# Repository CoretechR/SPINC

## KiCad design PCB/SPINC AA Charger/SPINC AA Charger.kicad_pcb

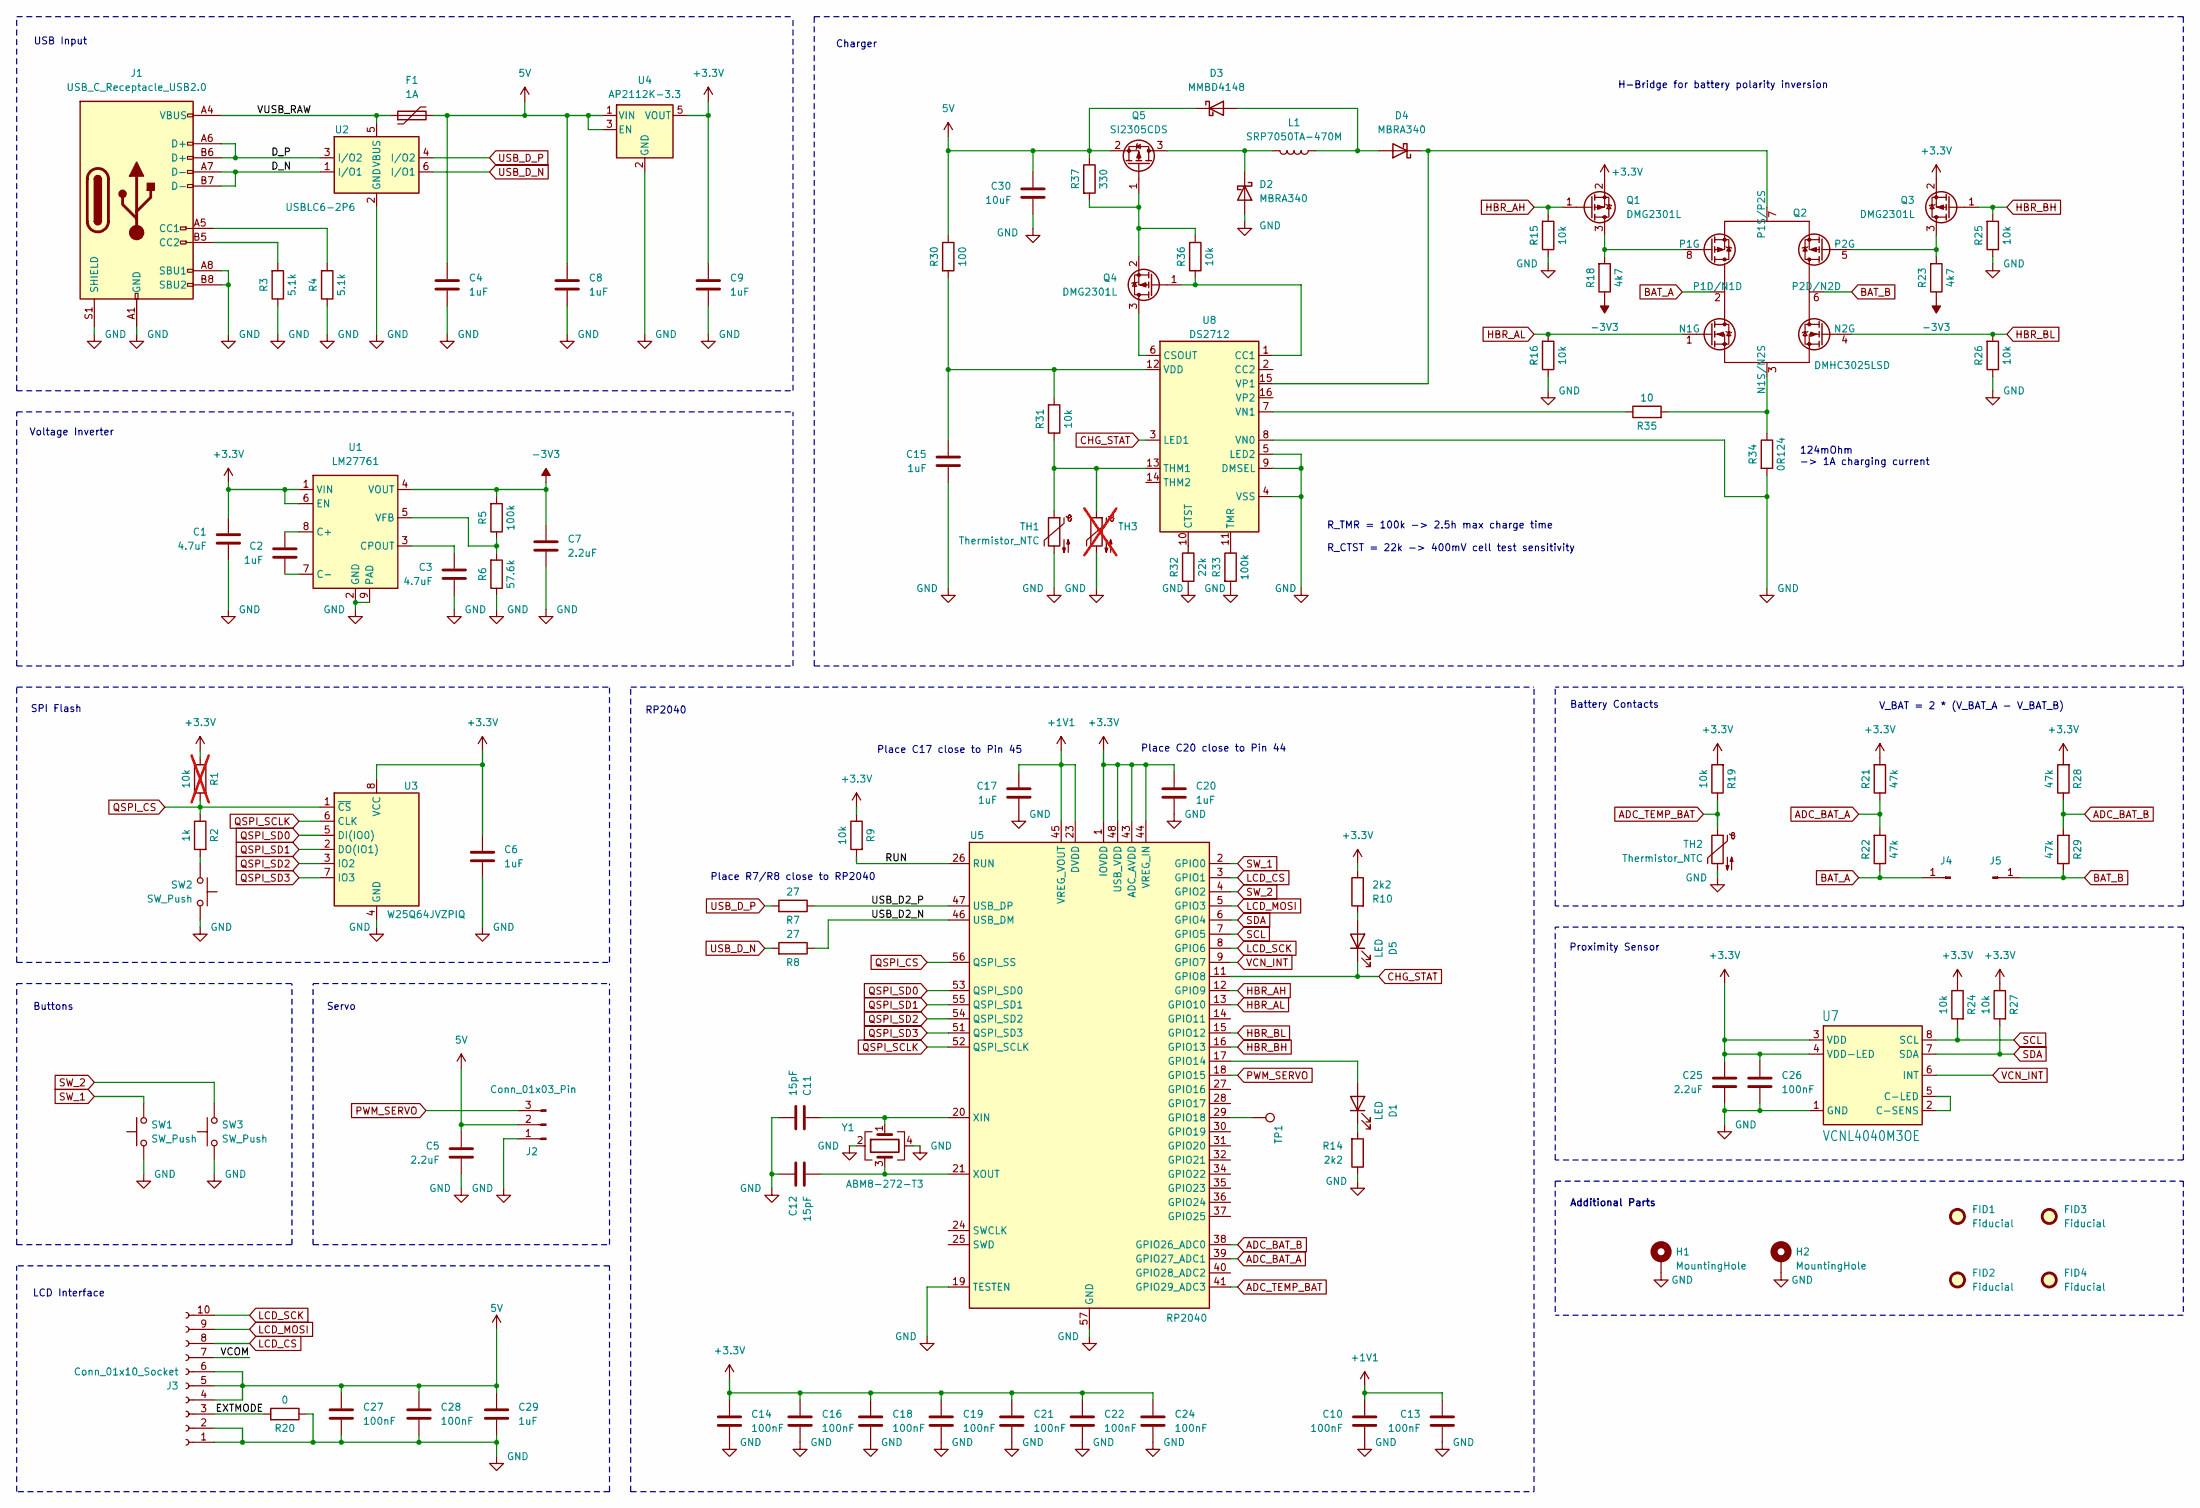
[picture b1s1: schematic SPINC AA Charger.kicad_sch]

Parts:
C1, C3: 4.7uF; C_0603_1608Metric; LCSC C1705
C2, C4, C6, C8, C9, C15, C17, C20, C29: 1uF; C_0603_1608Metric; LCSC C15849
C5, C7, C25: 2.2uF; C_0603_1608Metric; LCSC C913904
C10, C13, C14, C16, C18, C19, C21, C22, C24, C26, C27, C28: 100nF; C_0603_1608Metric; LCSC C1591
C11, C12: 15pF; C_0603_1608Metric; LCSC C107037
C30: 10uF; C_0603_1608Metric; LCSC C15850
D1, D5: LED; LED_0603_1608Metric; LCSC C965807
D2, D4: MBRA340; D_SMA; LCSC C26178
D3: MMBD4148; TSOT-23; LCSC C2928912
F1: 1A; Fuse_1206_3216Metric_Pad1.42x1.75mm_HandSolder; LCSC C151162
FID1, FID2, FID3, FID4: Fiducial; Fiducial_1mm_Mask2mm
H1, H2: MountingHole; MountingHole_3.2mm_M3_Pad_Via
J1: USB_C_Receptacle_USB2.0; USB_C_Receptacle_HRO_TYPE-C-31-M-12; LCSC C2982555
J2: Conn_01x03_Pin; PinHeader_1x03_P2.54mm_Vertical; LCSC C6332196
J3: Conn_01x10_Socket; 68711014022; LCSC C2919540
J4, J5: Conn_01x01_Pin; BatteryHolder_Keystone_590; LCSC C3029553
L1: SRP7050TA-470M; L_Bourns_SRP7050TA_7.3x6.6mm; LCSC C2047110
Q1, Q3, Q4: DMG2301L; SOT-23; LCSC C102619
Q2: DMHC3025LSD; SO-8_3.9x4.9mm_P1.27mm; LCSC C156387
Q5: SI2305CDS; SOT-23; LCSC C37577
R1: 10k; R_0603_1608Metric; not fitted
R2: 1k; R_0603_1608Metric; LCSC C22548
R3, R4: 5.1k; R_0603_1608Metric; LCSC C105580
R5, R33: 100k; R_0603_1608Metric; LCSC C14675
R6: 57.6k; R_0603_1608Metric; LCSC C245983
R7, R8: 27; R_0603_1608Metric; LCSC C137753
R9, R15, R16, R19, R24, R25, R26, R27, R31, R36: 10k; R_0603_1608Metric; LCSC C98220
R10, R14: 2k2; R_0603_1608Metric; LCSC C114662
R18, R23: 4k7; R_0603_1608Metric; LCSC C99782
R20: 0; R_0603_1608Metric; LCSC C116699
R21, R22, R28, R29: 47k; R_0603_1608Metric; LCSC C105579
R30: 100; R_0603_1608Metric; LCSC C125923
R32: 22k; R_0603_1608Metric; LCSC C114065
R34: 0R124; R_2512_6332Metric; LCSC C875831
R35: 10; R_0603_1608Metric; LCSC C109318
R37: 330; R_0603_1608Metric; LCSC C105881
SW1, SW3: SW_Push; Panasonic_EVQPUM_EVQPUD; LCSC C388642
SW2: SW_Push; SW_SPST_EVQP2; LCSC C2915174
TH1, TH2: Thermistor_NTC; R_0603_1608Metric; LCSC C13564
TH3: Thermistor_NTC; R_LDR_4.9x4.2mm_P2.54mm_Vertical; not fitted
TP1: TestPoint; TestPoint_Pad_D1.5mm
U1: LM27761; WSON-8-1EP_2x2mm_P0.5mm_EP0.9x1.6mm; LCSC C129351
U2: USBLC6-2P6; SOT-666; LCSC C2827693
U3: W25Q64JVZPIQ; WSON-8-1EP_6x5mm_P1.27mm_EP3.4x4.3mm; LCSC C2940197
U4: AP2112K-3.3; SOT-23-5; LCSC C51118
U5: RP2040; QFN-56-1EP_7x7mm_P0.4mm_EP3.2x3.2mm; LCSC C2040
U7: VCNL4040M3OE; VISHAY_VCNL4040_4X2X1.1; LCSC C142526
U8: DS2712; TSSOP-16_4.4x5mm_P0.65mm
Y1: ABM8-272-T3; Crystal_SMD_Abracon_ABM8G-4Pin_3.2x2.5mm; LCSC C20625731

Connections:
5V: C4.1, C5.1, C8.1, C27.1, C28.1, C29.1, C30.1, D3.3 (K), F1.2, J2.2, J3.4, J3.5, J3.6, Q5.2 (S), R30.1, R37.1, U4.1 (VIN), U4.3 (EN)
+1V1: C10.1, C13.1, C17.1, U5.23 (DVDD), U5.45 (VREG_VOUT), U5.50 (DVDD)
+3.3V: C1.1, C6.1, C9.1, C14.1, C16.1, C18.1, C19.1, C20.1, C21.1, C22.1, C24.1, C25.1, C26.1, Q1.2 (S), Q3.2 (S), R1.1, R9.1, R10.1, R19.2, R21.2, R24.1, R27.1, R28.2, U1.1 (VIN), U1.6 (EN), U3.8 (VCC), U4.5 (VOUT), U5.1 (IOVDD), U5.10 (IOVDD), U5.22 (IOVDD), U5.33 (IOVDD), U5.42 (IOVDD), U5.43 (ADC_AVDD), U5.44 (VREG_IN), U5.48 (USB_VDD), U5.49 (IOVDD), U7.3 (VDD), U7.4 (VDD-LED)
-3V3: C7.1, R5.2, R18.1, R23.1, U1.4 (VOUT)
/D_N: J1.A7 (D-), J1.B7 (D-), U2.1 (I/O1)
/D_P: J1.A6 (D+), J1.B6 (D+), U2.3 (I/O2)
/EXTMODE: J3.3, R20.2
/RUN: R9.2, U5.26 (RUN)
/USB_D2_N: R8.1, U5.46 (USB_DM)
/USB_D2_P: R7.1, U5.47 (USB_DP)
/VCOM: J3.7
/VUSB_RAW: F1.1, J1.A4 (VBUS), J1.A9 (VBUS), J1.B4 (VBUS), J1.B9 (VBUS), U2.5 (VBUS)
ADC_BAT_A: R21.1, R22.2, U5.39 (GPIO27_ADC1)
ADC_BAT_B: R28.1, R29.2, U5.38 (GPIO26_ADC0)
ADC_TEMP_BAT: R19.1, TH2.1, U5.41 (GPIO29_ADC3)
BAT_A: J4.1, Q2.2 (P1D/N1D), R22.1
BAT_B: J5.1, Q2.6 (P2D/N2D), R29.1
CHG_STAT: D5.1 (K), U5.11 (GPIO8), U8.3 (LED1)
GND: C1.2, C3.2, C4.2, C5.2, C6.2, C7.2, C8.2, C9.2, C10.2, C11.2, C12.1, C13.2, C14.2, C15.2, C16.2, C17.2, C18.2, C19.2, C20.2, C21.2, C22.2, C24.2, C25.2, C26.2, C27.2, C28.2, C29.2, C30.2, D2.2 (A), H1.1, H2.1, J1.A1 (GND), J1.A8 (SBU1), J1.A12 (GND), J1.B1 (GND), J1.B8 (SBU2), J1.B12 (GND), J1.S1 (SHIELD), J2.1, J3.1, J3.2, R3.1, R4.1, R6.1, R14.1, R15.1, R16.1, R20.1, R25.1, R26.1, R32.2, R33.2, R34.2, SW1.1, SW2.1, SW3.1, TH1.2, TH2.2, TH3.2, U1.2 (GND), U1.9 (PAD), U2.2 (GND), U3.4 (GND), U4.2 (GND), U5.19 (TESTEN), U5.57 (GND), U7.1 (GND), U8.4 (VSS), U8.5 (LED2), U8.8 (VN0), U8.9 (DMSEL), Y1.2, Y1.4
HBR_AH: Q1.1 (G), R15.2, U5.12 (GPIO9)
HBR_AL: Q2.1 (N1G), R16.2, U5.13 (GPIO10)
HBR_BH: Q3.1 (G), R25.2, U5.16 (GPIO13)
HBR_BL: Q2.4 (N2G), R26.2, U5.15 (GPIO12)
LCD_CS: J3.8, U5.3 (GPIO1)
LCD_MOSI: J3.9, U5.5 (GPIO3)
LCD_SCK: J3.10, U5.8 (GPIO6)
unnamed: D1.2 (A), U5.17 (GPIO14)
unnamed: D1.1 (K), R14.2
unnamed: D2.1 (K), L1.2, Q5.3 (D)
unnamed: D3.1 (A), D4.2 (A), L1.1
unnamed: D4.1 (K), Q2.7 (P1S/P2S), U8.15 (VP1)
unnamed: D5.2 (A), R10.2
unnamed: J1.A5 (CC1), R4.2
unnamed: J1.B5 (CC2), R3.2
unnamed: Q1.3 (D), Q2.8 (P1G), R18.2
unnamed: Q2.3 (N1S/N2S), R34.1, R35.2
unnamed: Q2.5 (P2G), Q3.3 (D), R23.2
unnamed: Q4.3 (D), U8.6 (CSOUT)
unnamed: Q4.1 (G), R36.1, U8.1 (CC1)
unnamed: Q4.2 (S), Q5.1 (G), R36.2, R37.2
unnamed: R2.2, SW2.2
unnamed: C2.1, U1.8 (C+)
unnamed: C2.2, U1.7 (C-)
unnamed: C3.1, U1.3 (CPOUT)
unnamed: R5.1, R6.2, U1.5 (VFB)
unnamed: TP1.1, U5.29 (GPIO18)
unnamed: C11.1, U5.20 (XIN), Y1.1
unnamed: C12.2, U5.21 (XOUT), Y1.3
unnamed: U7.2 (C-SENS), U7.5 (C-LED)
unnamed: R32.1, U8.10 (CTST)
unnamed: R31.1, TH1.1, TH3.1, U8.13 (THM1)
unnamed: R33.1, U8.11 (TMR)
unnamed: C15.1, R30.2, R31.2, U8.12 (VDD)
unnamed: R35.1, U8.7 (VN1)
PWM_SERVO: J2.3, U5.18 (GPIO15)
QSPI_CS: R1.2, R2.1, U3.1 (~CS), U5.56 (QSPI_SS)
QSPI_SCLK: U3.6 (CLK), U5.52 (QSPI_SCLK)
QSPI_SD0: U3.5 (DI(IO0)), U5.53 (QSPI_SD0)
QSPI_SD1: U3.2 (DO(IO1)), U5.55 (QSPI_SD1)
QSPI_SD2: U3.3 (IO2), U5.54 (QSPI_SD2)
QSPI_SD3: U3.7 (IO3), U5.51 (QSPI_SD3)
SCL: R24.2, U5.7 (GPIO5), U7.8 (SCL)
SDA: R27.2, U5.6 (GPIO4), U7.7 (SDA)
SW_1: SW1.2, U5.2 (GPIO0)
SW_2: SW3.2, U5.4 (GPIO2)
USB_D_N: R8.2, U2.6 (I/O1)
USB_D_P: R7.2, U2.4 (I/O2)
VCN_INT: U5.9 (GPIO7), U7.6 (INT)

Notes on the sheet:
RP2040
Place C17 close to Pin 45
Voltage Inverter
Buttons
Charger
H-Bridge for battery polarity inversion
Place R7/R8 close to RP2040
SPI Flash
Battery Contacts
Additional Parts
Place C20 close to Pin 44
Servo
V_BAT = 2 * (V_BAT_A - V_BAT_B)
LCD Interface
USB Input
Proximity Sensor
124mOhm -> 1A charging current
R_TMR = 100k -> 2.5h max charge time R_CTST = 22k -> 400mV cell test sensitivity

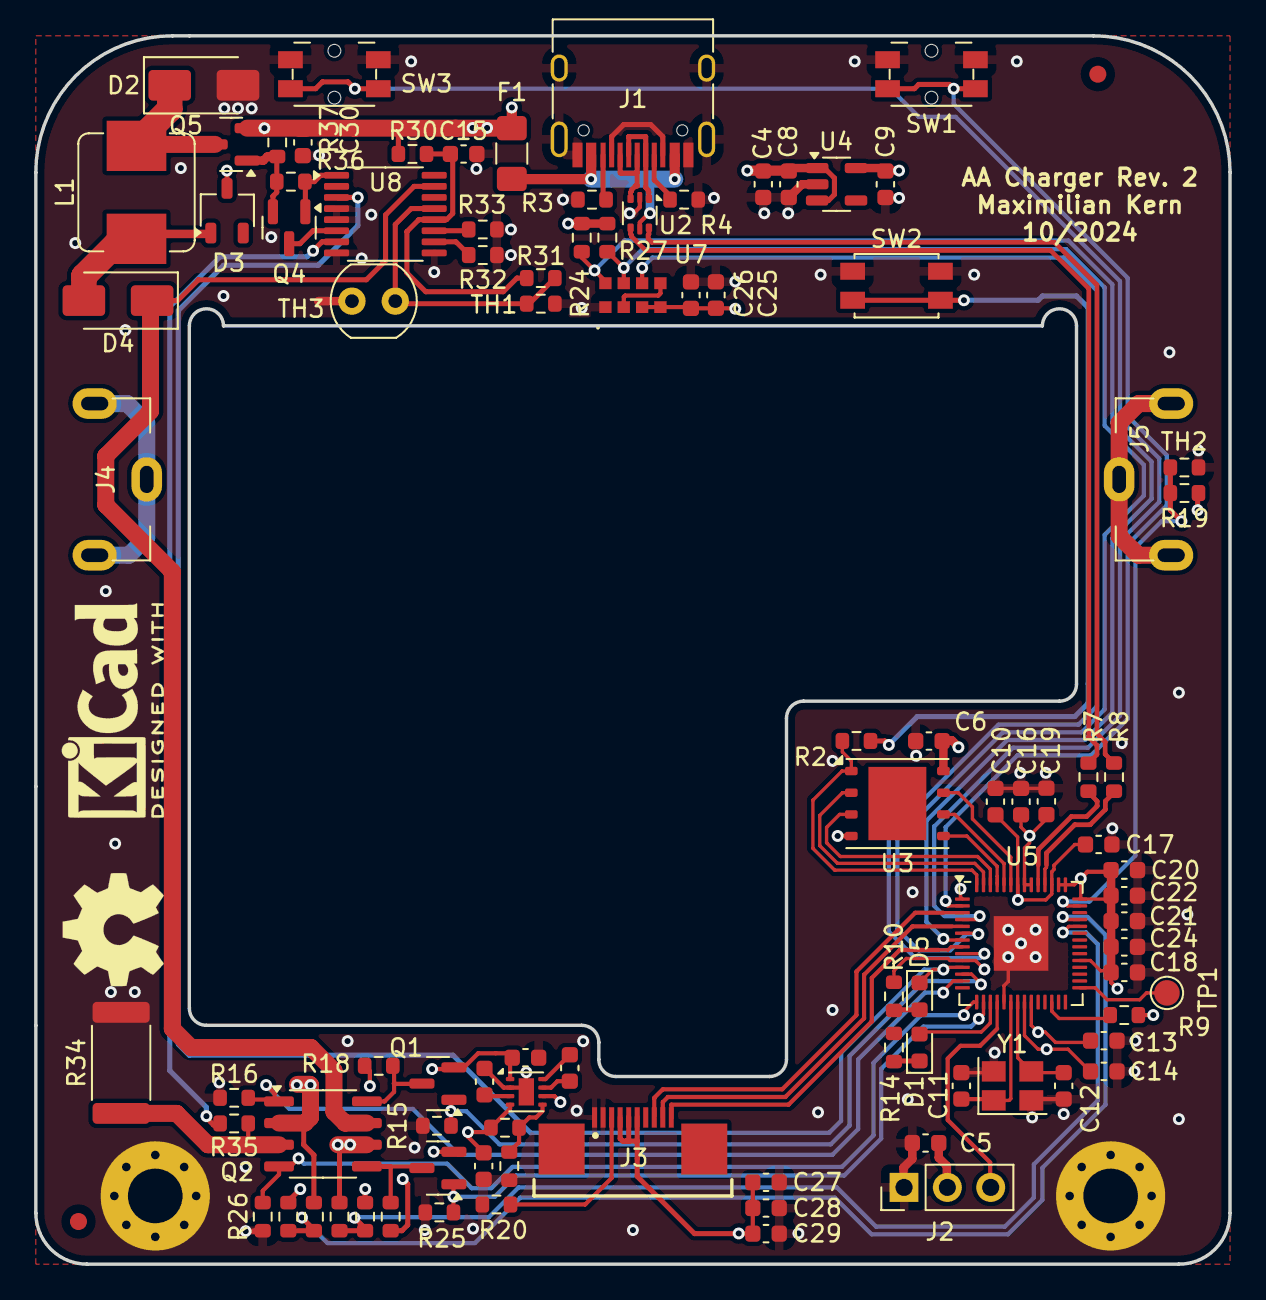
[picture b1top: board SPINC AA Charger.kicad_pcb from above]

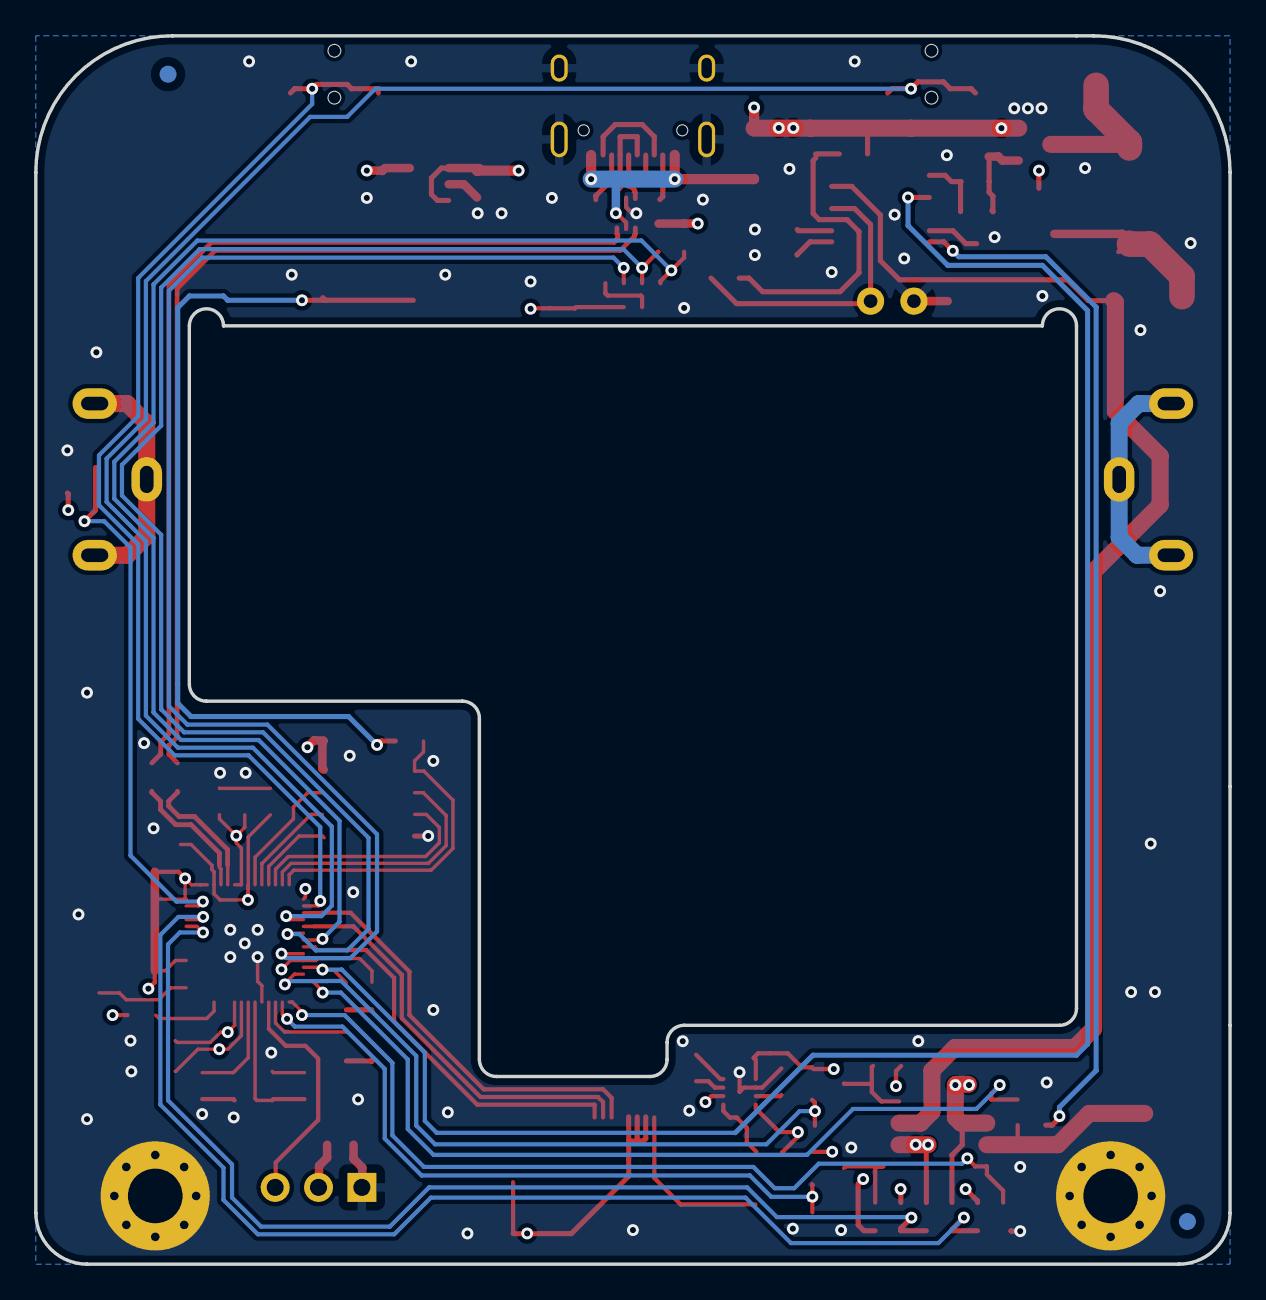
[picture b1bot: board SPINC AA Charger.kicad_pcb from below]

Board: 4 copper layers, 70.0 x 72.0 mm, 99 parts (2 on the bottom side), 67 nets.

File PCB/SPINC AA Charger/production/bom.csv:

Designator,Footprint,Quantity,Value,LCSC Part #
"C1, C3",0603,2,4.7uF,C1705
"C10, C13, C14, C16, C18, C19, C21, C22, C24, C26, C27, C28",0603,12,100nF,C1591
"C11, C12",0603,2,15pF,C107037
"C15, C17, C2, C20, C29, C4, C6, C8, C9",0603,9,1uF,C15849
"C25, C5, C7",0603,3,2.2uF,C913904
C30,0603,1,10uF,C15850
"D1, D5",0603,2,LED,C965807
"D2, D4",D_SMA,2,MBRA340, C26178
D3,TSOT-23,1,MMBD4148, C2928912
F1,1206,1,1A,C151162
J1,USB_C_Receptacle_HRO_TYPE-C-31-M-12,1,USB_C_Receptacle_USB2.0,C2982555
J2,PinHeader_1x03_P2.54mm_Vertical,1,Conn_01x03_Pin, C6332196
J3,68711014022,1,Conn_01x10_Socket,C2919540
"J4, J5",BatteryHolder_Keystone_590,2,Conn_01x01_Pin,C3029553
L1,L_Bourns_SRP7050TA_7.3x6.6mm,1,SRP7050TA-470M, C2047110
"Q1, Q3, Q4",SOT-23,3,DMG2301L,C102619
Q2,SO-8_3.9x4.9mm_P1.27mm,1,DMHC3025LSD,C156387
Q5,SOT-23,1,SI2305CDS,C37577
"R10, R14",0603,2,2k2,C114662
"R15, R16, R19, R24, R25, R26, R27, R31, R36, R9",0603,10,10k,C98220
"R18, R23",0603,2,4k7, C99782
R2,0603,1,1k,C22548
R20,0603,1,0,C116699
"R21, R22, R28, R29",0603,4,47k, C105579
"R3, R4",0603,2,5.1k,C105580
R30,0603,1,100,C125923
R32,0603,1,22k,C114065
"R33, R5",0603,2,100k,C14675
R34,2512,1,0R124,C875831
R35,0603,1,10,C109318
R37,0603,1,330,C105881
R6,0603,1,57.6k, C245983
"R7, R8",0603,2,27,C137753
"SW1, SW3",Panasonic_EVQPUM_EVQPUD,2,SW_Push,C388642
SW2,SW_SPST_EVQP2,1,SW_Push,C2915174
"TH1, TH2",0603,2,Thermistor_NTC,C13564
U1,WSON-8-1EP_2x2mm_P0.5mm_EP0.9x1.6mm,1,LM27761,C129351
U2,SOT-666,1,USBLC6-2P6,C2827693
U3,WSON-8-1EP_6x5mm_P1.27mm_EP3.4x4.3mm,1,W25Q64JVZPIQ,C2940197
U4,SOT-23-5,1,AP2112K-3.3,C51118
U5,QFN-56-1EP_7x7mm_P0.4mm_EP3.2x3.2mm,1,RP2040, C2040
U7,VISHAY_VCNL4040_4X2X1.1,1,VCNL4040M3OE,C142526
U8,TSSOP-16_4.4x5mm_P0.65mm,1,DS2712,
Y1,Crystal_SMD_Abracon_ABM8G-4Pin_3.2x2.5mm,1,ABM8-272-T3,C20625731

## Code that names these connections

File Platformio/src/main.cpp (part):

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
// Pin assignment -----------------------------------------------------------------------------------------------------------------------

#define SW_A 2 // SW_2
#define SW_B 0 // SW_1
#define USER_LED 14 // 25 for Pico

#define LCD_CS 1
#define LCD_MOSI 3
#define LCD_SCK 6

#define SDA 4
#define SCL 5
#define VCN_INT 7

#define CHG_STAT 8
#define CHG_TMR 11

#define PWM_SERVO 15

#define HBR_AH 9
#define HBR_AL 10
#define HBR_BL 12
#define HBR_BH 13

#define ADC_BAT_A A0
#define ADC_BAT_B A1
#define ADC_TEMP_BAT A3

// H-bridge declarations
enum HBR_STATE {OFF, A_POS, B_POS};
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  pinMode(SW_A, INPUT_PULLUP);

  // Proximity Sensor Interrupt
  pinMode(VCN_INT, INPUT);

  // H-Bridge Controls
  pinMode(HBR_AL, OUTPUT);
  pinMode(HBR_AH, OUTPUT);
  pinMode(HBR_BL, OUTPUT);
  pinMode(HBR_BH, OUTPUT);
  pinMode(ADC_BAT_A, INPUT);
  pinMode(ADC_BAT_B, INPUT);
  pinMode(ADC_TEMP_BAT, INPUT);

  // Charger
  pinMode(CHG_STAT, INPUT_PULLUP);
  pinMode(CHG_TMR, INPUT);
  
  // Servo
  pinMode(PWM_SERVO, OUTPUT);

  //LCD
  pinMode(LCD_CS, OUTPUT); // this line is important since the adafruit library was ported to HW SPI!

  // Serial Init
  Serial.begin(115200);
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
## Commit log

2025-01-27 LCSC part numbers fixed
    - assigned LCSC part numbers properly to the BOM
2025-03-23 Added the option to switch 24h/12h formats (#6)
2025-03-26 fix: show charging status as two lines one for voltage and one for battery fill icon, so there's no twitching due to variable text length
2025-03-28 feat: basic language support
2026-05-19 Added CAD source files + STEP export
    see #15 and #16
